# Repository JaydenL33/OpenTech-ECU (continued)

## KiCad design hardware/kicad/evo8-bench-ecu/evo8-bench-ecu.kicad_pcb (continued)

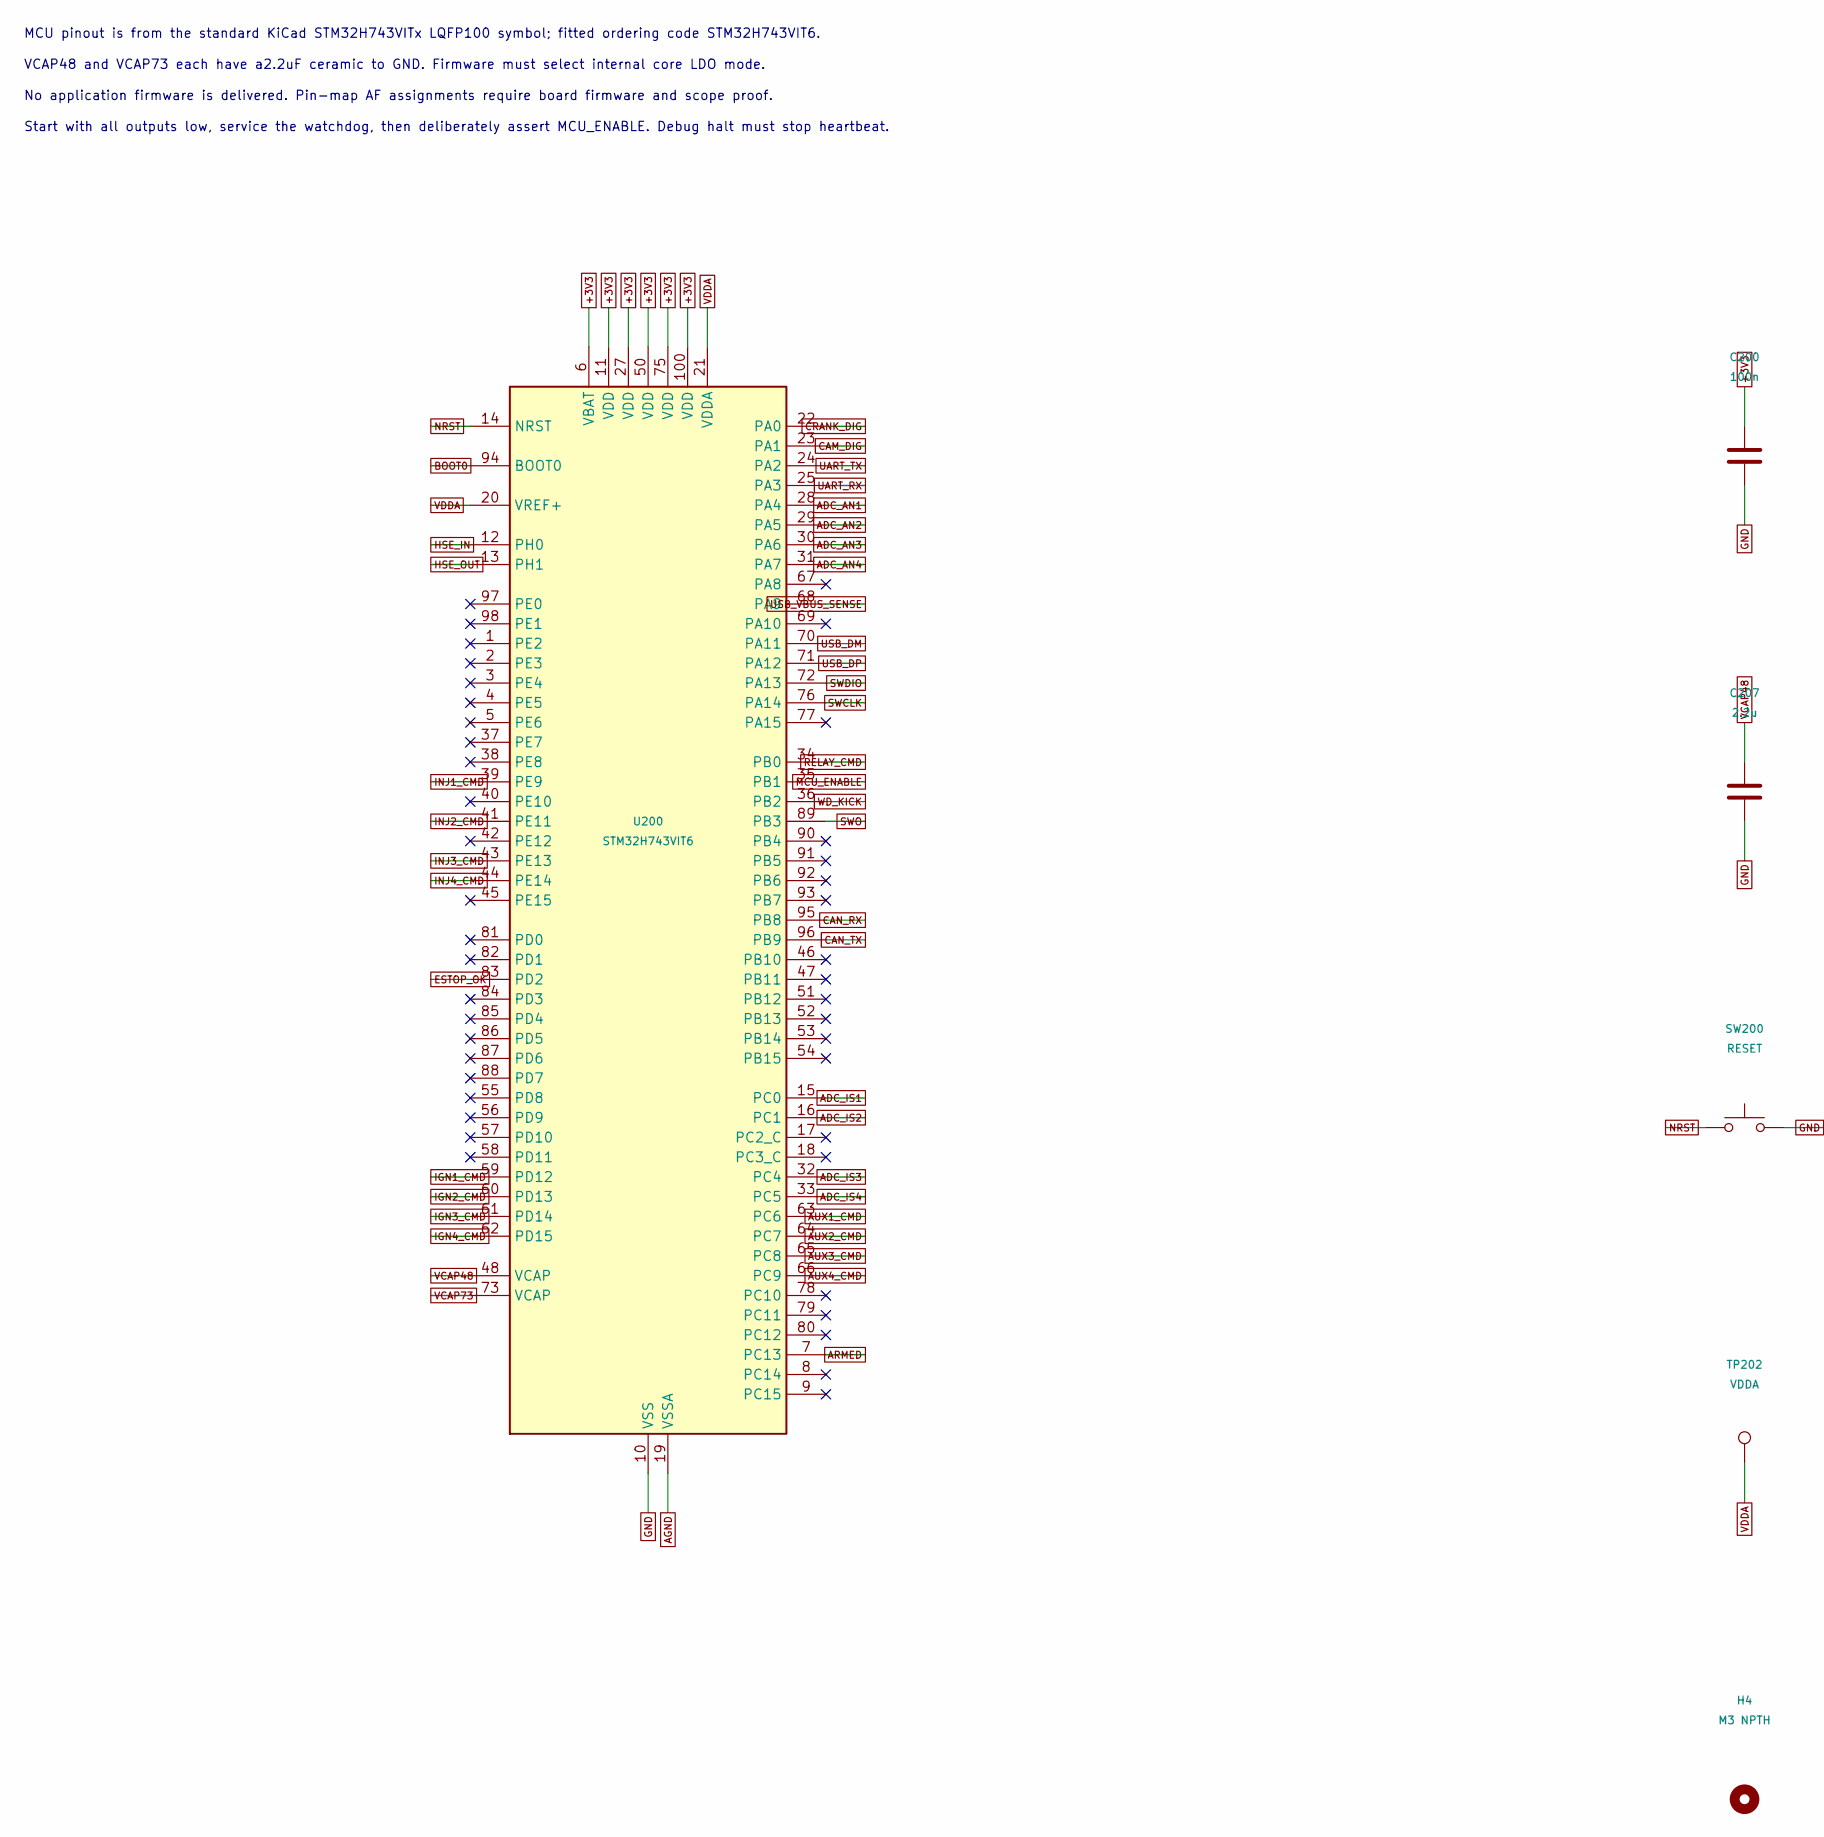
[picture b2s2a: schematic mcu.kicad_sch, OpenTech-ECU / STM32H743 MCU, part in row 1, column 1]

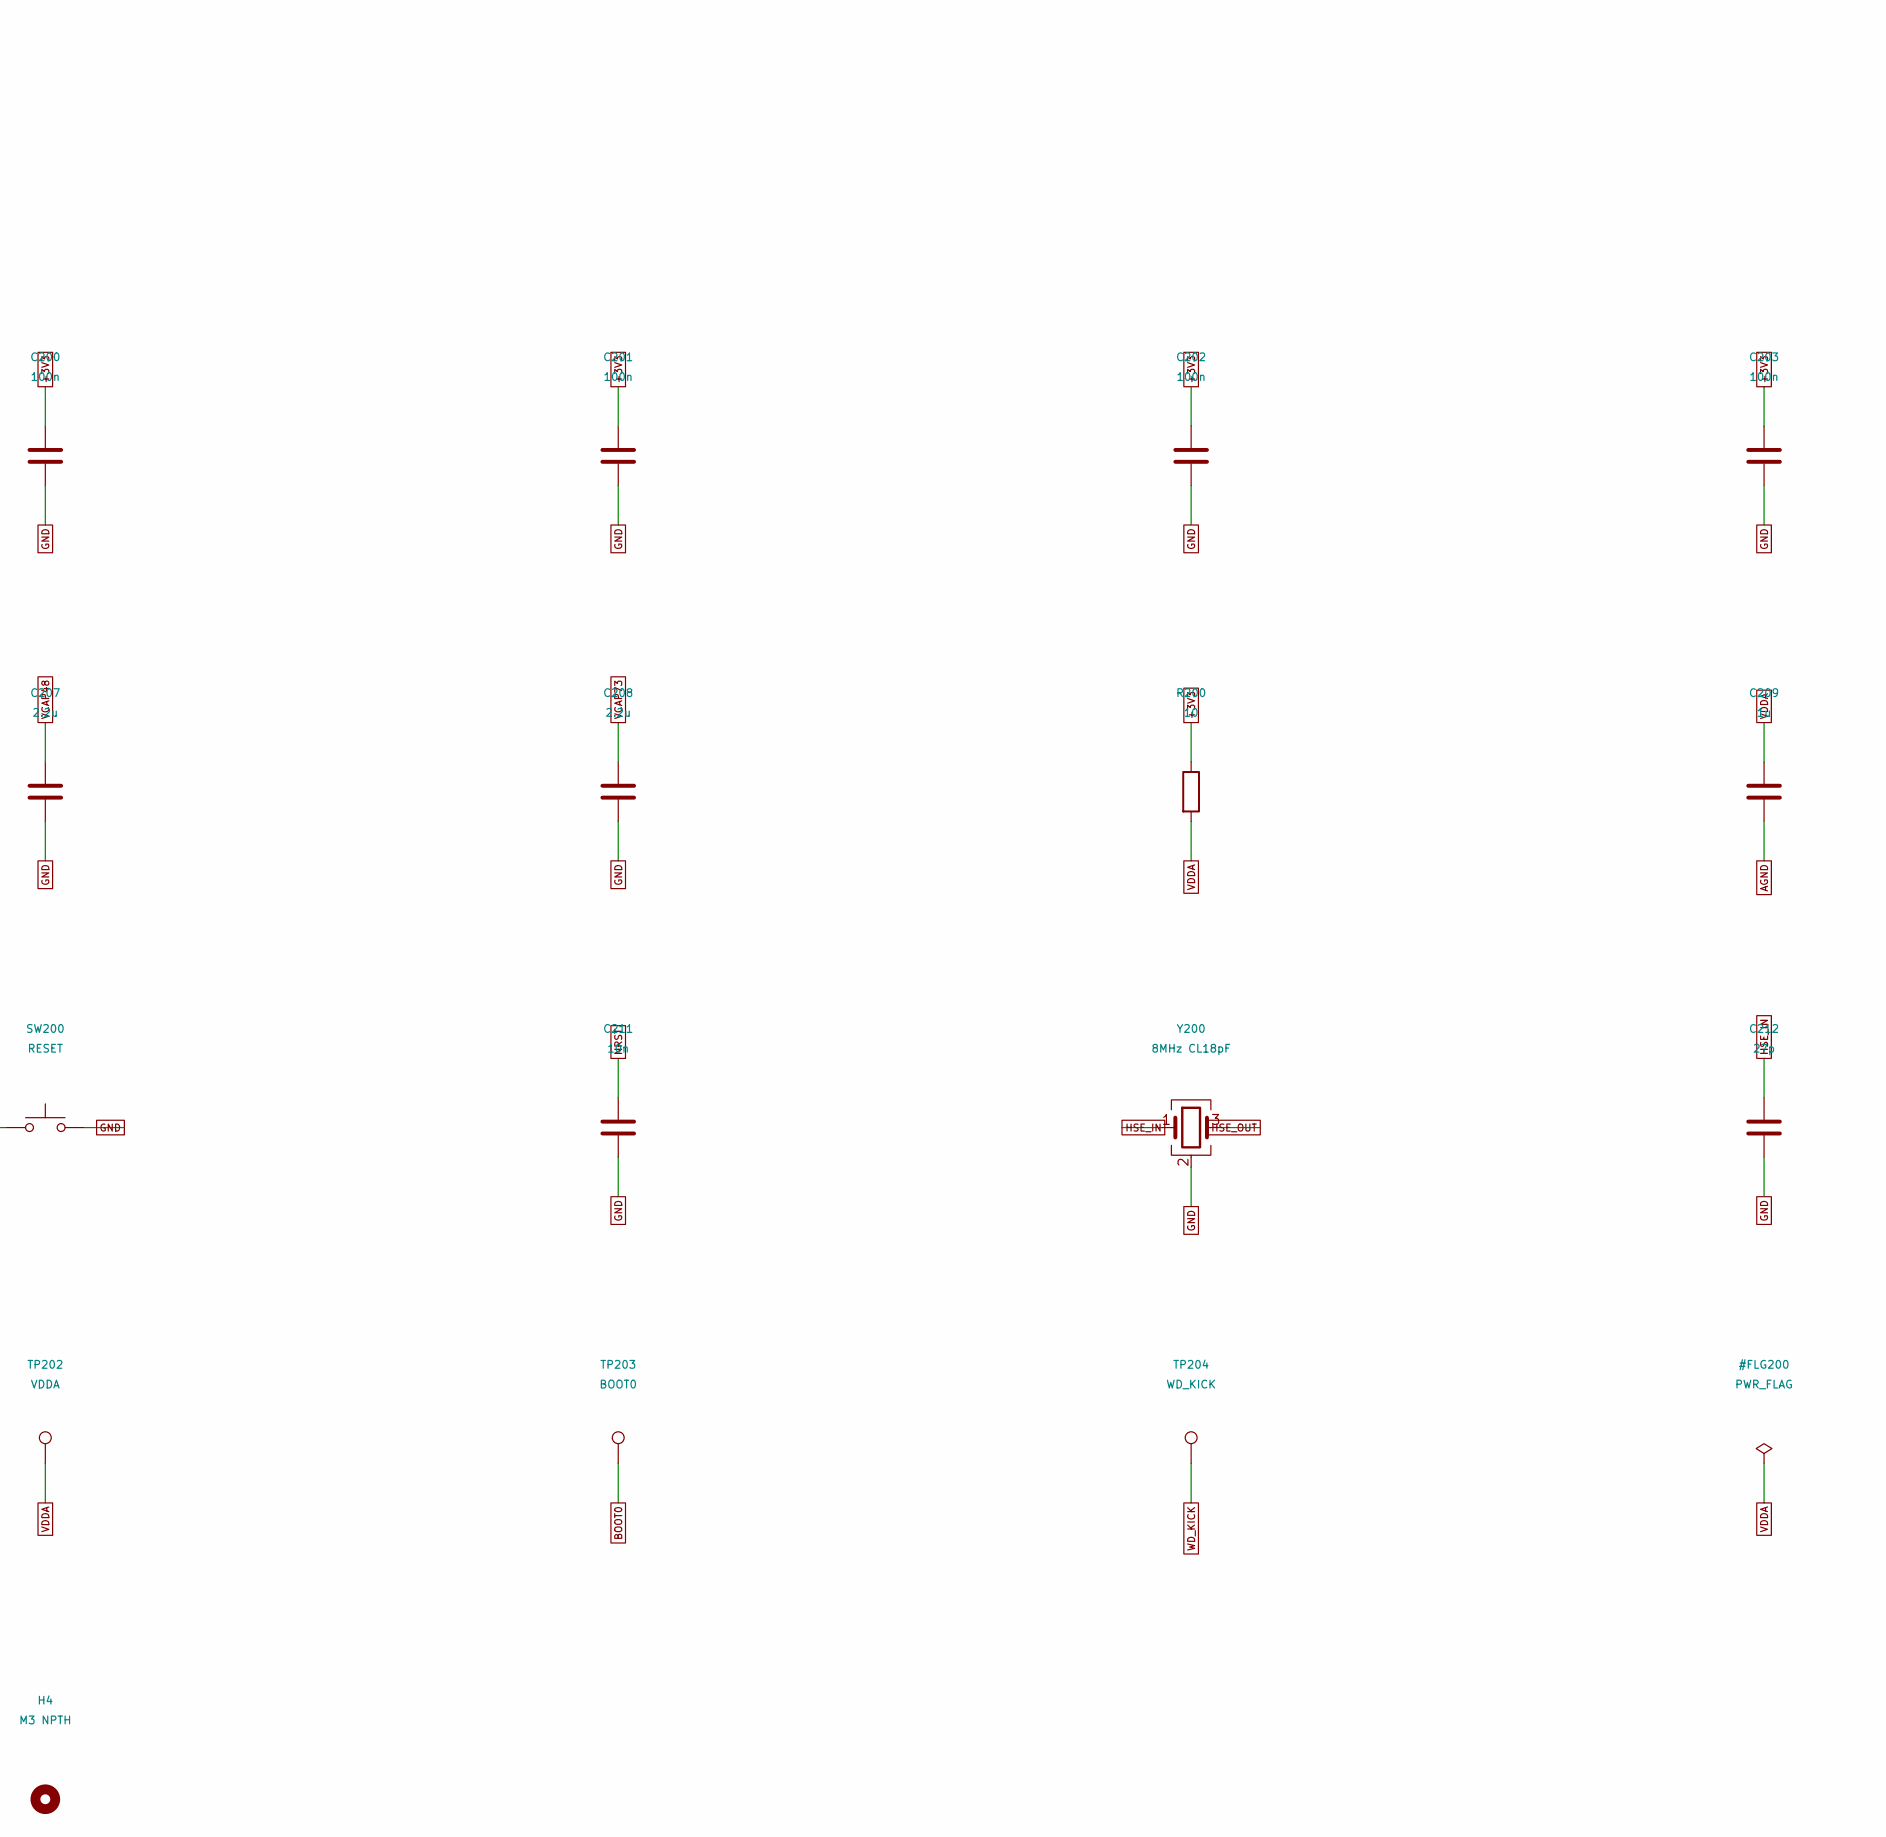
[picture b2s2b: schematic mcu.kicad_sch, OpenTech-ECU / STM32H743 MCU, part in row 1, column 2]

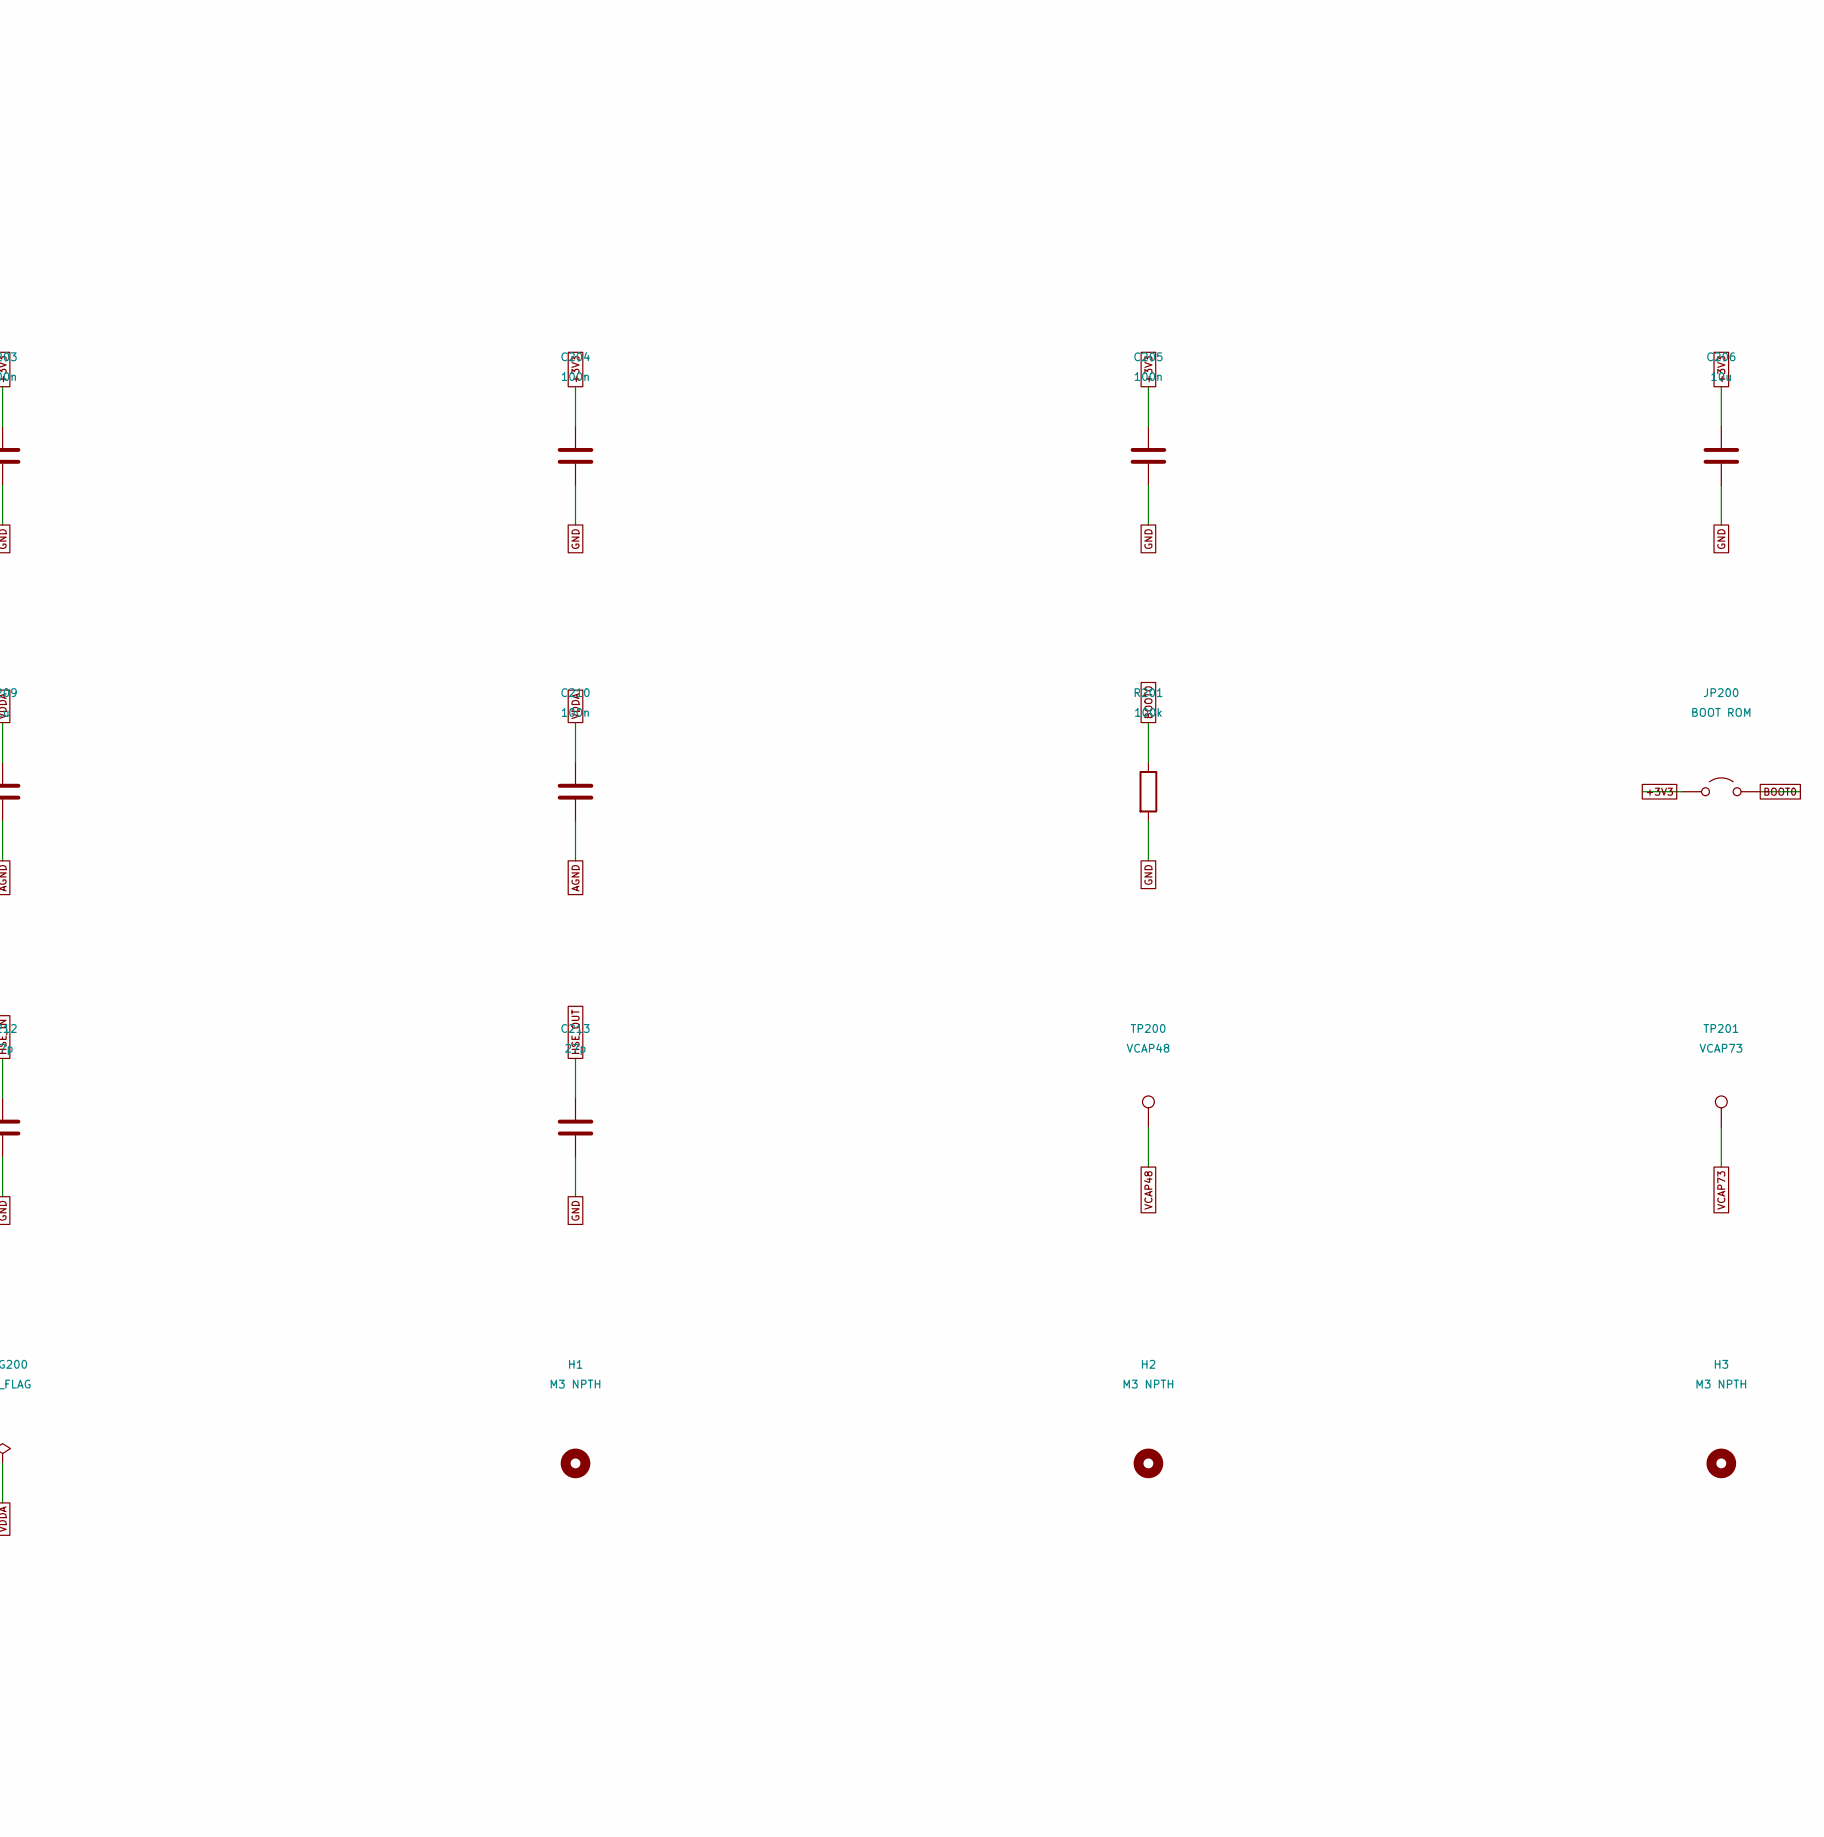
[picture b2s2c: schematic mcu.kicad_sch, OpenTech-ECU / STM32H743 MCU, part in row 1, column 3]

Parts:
C200, C201, C202, C203, C204, C205, C210: 100n; C_0805_2012Metric; MPN GRM21BR71H104KA01L
C206: 10u; C_0805_2012Metric; MPN GRM21BR61A106KE19L
C207, C208: 2.2u; C_0805_2012Metric; MPN GRM21BR71C225KA12L
C209: 1u; C_0805_2012Metric; MPN GRM21BR71H105KA12L
C211: 10n; C_0805_2012Metric; MPN GRM21BR71H103KA01L
C212, C213: 27p; C_0805_2012Metric; MPN GRM21A5C1H270JA01D
H1, H2, H3, H4: M3 NPTH; MountingHole_3.2mm_M3
JP200: BOOT ROM; PinHeader_1x02_P2.54mm_Vertical; MPN 61300211121
R200: 10; R_0805_2012Metric; MPN RC0805FR-0710RL
R201: 100k; R_0805_2012Metric; MPN RC0805FR-07100KL
SW200: RESET; SW_PUSH_6mm; MPN B3F-1000
TP200: VCAP48; TestPoint_THTPad_D2.0mm_Drill1.0mm; MPN 5010
TP201: VCAP73; TestPoint_THTPad_D2.0mm_Drill1.0mm; MPN 5010
TP202: VDDA; TestPoint_THTPad_D2.0mm_Drill1.0mm; MPN 5010
TP203: BOOT0; TestPoint_THTPad_D2.0mm_Drill1.0mm; MPN 5010
TP204: WD_KICK; TestPoint_THTPad_D2.0mm_Drill1.0mm; MPN 5010
U200: STM32H743VIT6; LQFP-100_14x14mm_P0.5mm; MPN STM32H743VIT6
Y200: 8MHz CL18pF; Crystal_SMD_3225-4Pin_3.2x2.5mm; MPN ABM8-8.000MHZ-B2-T

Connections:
+3V3: C200.1, C201.1, C202.1, C203.1, C204.1, C205.1, C206.1, JP200.1 (A), R200.1, U200.6 (VBAT), U200.11 (VDD), U200.27 (VDD), U200.50 (VDD), U200.75 (VDD), U200.100 (VDD); also elsewhere on the board
ADC_AN1: U200.28 (PA4); also elsewhere on the board
ADC_AN2: U200.29 (PA5); also elsewhere on the board
ADC_AN3: U200.30 (PA6); also elsewhere on the board
ADC_AN4: U200.31 (PA7); also elsewhere on the board
ADC_IS1: U200.15 (PC0); also elsewhere on the board
ADC_IS2: U200.16 (PC1); also elsewhere on the board
ADC_IS3: U200.32 (PC4); also elsewhere on the board
ADC_IS4: U200.33 (PC5); also elsewhere on the board
AGND: C209.2, C210.2, U200.19 (VSSA); also elsewhere on the board
ARMED: U200.7 (PC13); also elsewhere on the board
AUX1_CMD: U200.63 (PC6); also elsewhere on the board
AUX2_CMD: U200.64 (PC7); also elsewhere on the board
AUX3_CMD: U200.65 (PC8); also elsewhere on the board
AUX4_CMD: U200.66 (PC9); also elsewhere on the board
BOOT0: JP200.2 (B), R201.1, TP203.1, U200.94 (BOOT0)
CAM_DIG: U200.23 (PA1); also elsewhere on the board
CAN_RX: U200.95 (PB8); also elsewhere on the board
CAN_TX: U200.96 (PB9); also elsewhere on the board
CRANK_DIG: U200.22 (PA0); also elsewhere on the board
ESTOP_OK: U200.83 (PD2); also elsewhere on the board
GND: C200.2, C201.2, C202.2, C203.2, C204.2, C205.2, C206.2, C207.2, C208.2, C211.2, C212.2, C213.2, R201.2, SW200.2, U200.10 (VSS), U200.26 (VSS), U200.49 (VSS), U200.74 (VSS), U200.99 (VSS), Y200.2 (G), Y200.4 (G); also elsewhere on the board
HSE_IN: C212.1, U200.12 (PH0), Y200.1
HSE_OUT: C213.1, U200.13 (PH1), Y200.3
IGN1_CMD: U200.59 (PD12); also elsewhere on the board
IGN2_CMD: U200.60 (PD13); also elsewhere on the board
IGN3_CMD: U200.61 (PD14); also elsewhere on the board
IGN4_CMD: U200.62 (PD15); also elsewhere on the board
INJ1_CMD: U200.39 (PE9); also elsewhere on the board
INJ2_CMD: U200.41 (PE11); also elsewhere on the board
INJ3_CMD: U200.43 (PE13); also elsewhere on the board
INJ4_CMD: U200.44 (PE14); also elsewhere on the board
MCU_ENABLE: U200.35 (PB1); also elsewhere on the board
NRST: C211.1, SW200.1, U200.14 (NRST); also elsewhere on the board
RELAY_CMD: U200.34 (PB0); also elsewhere on the board
SWCLK: U200.76 (PA14); also elsewhere on the board
SWDIO: U200.72 (PA13); also elsewhere on the board
SWO: U200.89 (PB3); also elsewhere on the board
UART_RX: U200.25 (PA3); also elsewhere on the board
UART_TX: U200.24 (PA2); also elsewhere on the board
USB_DM: U200.70 (PA11); also elsewhere on the board
USB_DP: U200.71 (PA12); also elsewhere on the board
USB_VBUS_SENSE: U200.68 (PA9); also elsewhere on the board
VCAP48: C207.1, TP200.1, U200.48 (VCAP)
VCAP73: C208.1, TP201.1, U200.73 (VCAP)
VDDA: C209.1, C210.1, R200.2, TP202.1, U200.20 (VREF+), U200.21 (VDDA)
WD_KICK: TP204.1, U200.36 (PB2); also elsewhere on the board

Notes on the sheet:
MCU pinout is from the standard KiCad STM32H743VITx LQFP100 symbol; fitted ordering code STM32H743VIT6.
VCAP48 and VCAP73 each have a2.2uF ceramic to GND. Firmware must select internal core LDO mode.
No application firmware is delivered. Pin-map AF assignments require board firmware and scope proof.
Start with all outputs low, service the watchdog, then deliberately assert MCU_ENABLE. Debug halt must stop heartbeat.
